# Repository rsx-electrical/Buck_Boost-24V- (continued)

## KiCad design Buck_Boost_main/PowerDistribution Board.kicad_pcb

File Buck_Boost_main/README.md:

# PowerDistributionBoard
 Distribution power to 150A PDP, 20A 12V regulator, 30A 19V regulator + 24V regulator + charger.

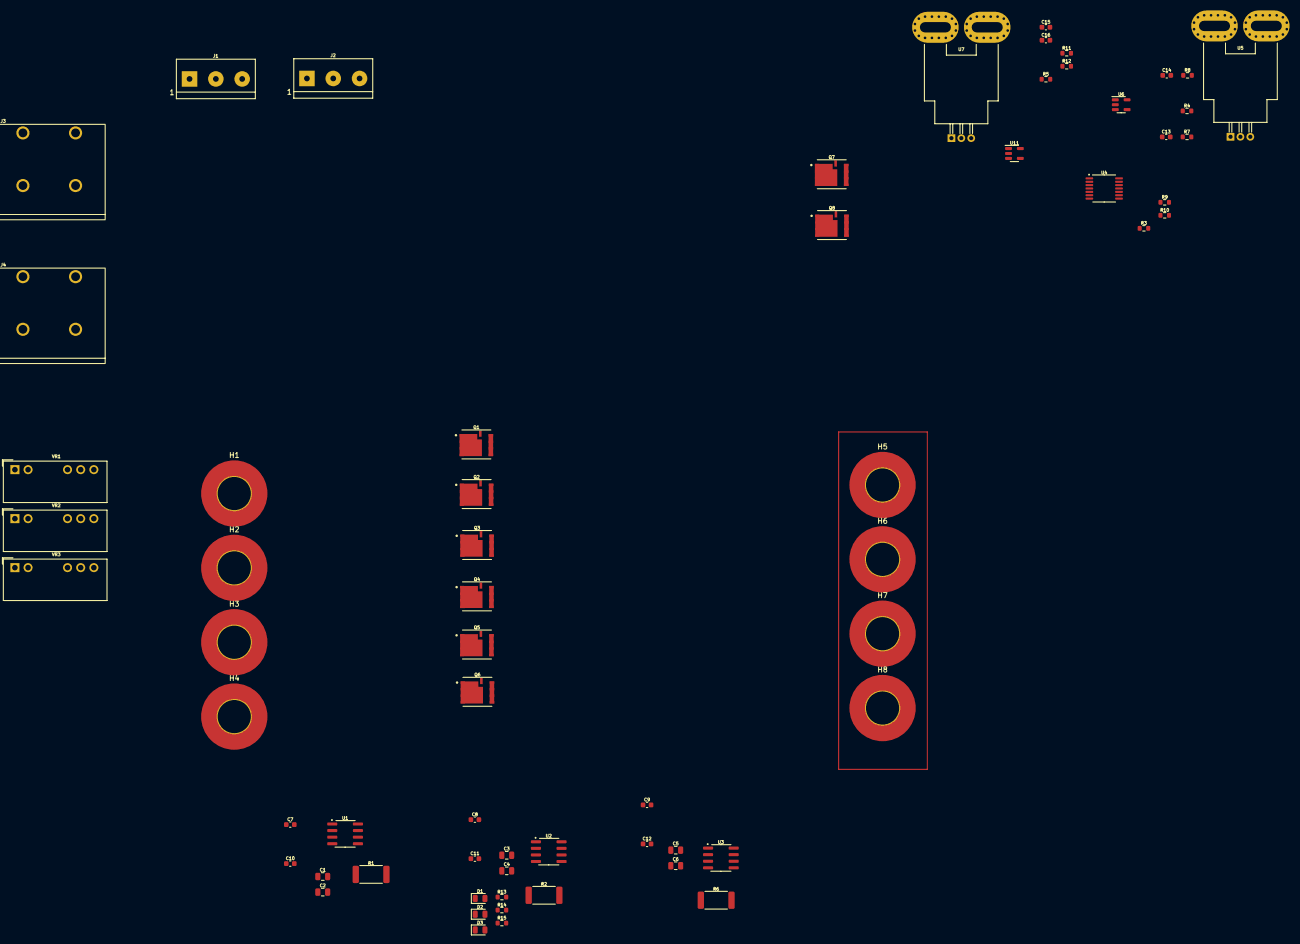
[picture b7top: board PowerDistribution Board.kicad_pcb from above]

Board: 2 copper layers, 65 parts (0 on the bottom side), 41 nets, no tracks yet.

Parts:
C1, C2, C3, C4, C5, C6: 1u; C_0805_2012Metric
C7, C8, C9, C10, C11, C12, C13, C14, C15, C16: 0u1; C_0603_1608Metric
D1, D2, D3: LED_B; LED_0805_2012Metric
H1, H2, H3, H4, H5, H6, H7, H8: MountingHole_Pad; MountingHole_6.4mm_M6_Pad_TopBottom
J1, J2: Screw_Terminal_3x5.08; Molex_0398800303
J3, J4: Screw_Terminal_2x10.16; Amphenol_VP0265540000G
Q1, Q2, Q3, Q4, Q5, Q6, Q7, Q8: IQDH29NE2LM5CG; IFX-PG-TTFN-9-2-V
R1, R2, R6: 1R00_1W; R_2512_6332Metric
R3, R4, R9, R10, R13, R14, R15: 1K; R_0603_1608Metric
R5, R7, R8, R12: 10K; R_0603_1608Metric
R11: 5.6K; R_0603_1608Metric
U1, U2, U3: NCV57080ADR2G; SOIC-8_3.9x4.9mm_P1.27mm_DL
U4: 74HC08; TSSOP-14_4.4x5mm_P0.65mm_DL
U5: ACS758ECB-200U-PFF-T; Allegro_CB_PFF
U6, U11: LMV321A; SOT-23-5
U7: ACS758LCB-050U-PFF-T; Allegro_CB_PFF
VR1, VR2, VR3: NMK1212SAC; Converter_DCDC_muRata_NMKDxxxxSAC_THT

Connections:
12V reg: C4.2, C11.2, J3.1, Q7.1 (S), Q7.2 (S), Q7.3 (S), Q7.4 (S), U2.8 (GND2), VR2.7 (0V)
12V_Gate: Q7.9 (G), R2.2, U2.7 (CLAMP)
12V_Iso_12V: C4.1, C11.1, D2.1 (K), U2.5 (VDD2)
12V_Iso_12V_LED: R14.1, VR2.5 (+Vo)
12V_Iso_19V: C1.1, C10.1, D3.1 (K), U1.5 (VDD2)
12V_Iso_19V_LED: R15.1, VR3.5 (+Vo)
12V_Iso_PDP: C6.1, C12.1, D1.1 (K), U3.5 (VDD2)
12V_Iso_PDP_LED: R13.1, VR1.5 (+Vo)
19V reg: C1.2, C10.2, J3.2, Q8.1 (S), Q8.2 (S), Q8.3 (S), Q8.4 (S), U1.8 (GND2), U7.5 (IP-), VR3.7 (0V)
19V_Gate: Q8.9 (G), R1.2, U1.7 (CLAMP)
30A Ref+: R5.2, R11.1, U11.3 (+)
150A Ref+: R4.2, R7.1, U6.3 (+)
+3V3: C2.1, C3.1, C5.1, C7.1, C8.1, C9.1, C14.2, C16.2, J1.2, R4.1, R5.1, U1.1 (VDD1), U2.1 (VDD1), U3.1 (VDD1), U4.2, U4.5, U4.14 (VCC), U5.1 (VCC), U6.5 (V+), U7.1 (VCC), U11.5 (V+)
+12V: J1.3, VR1.1 (Vin), VR2.1 (Vin), VR3.1 (Vin)
Charger_in: J4.2, U7.4 (IP+)
Enable1: J2.1, U4.13
Enable2: J2.2, R9.1
Enable3: J2.3, U4.10
GND: C2.2, C3.2, C5.2, C7.2, C8.2, C9.2, C13.2, C14.1, C15.2, C16.1, J1.1, R7.2, R11.2, U1.3 (C), U1.4 (GND1), U2.3 (C), U2.4 (GND1), U3.3 (C), U3.4 (GND1), U4.7 (GND), U5.2 (GND), U6.2 (V-), U7.2 (GND), U11.2 (V-), VR1.2 (GND), VR2.2 (GND), VR3.2 (GND)
IN+1: R3.2, U1.2 (A)
IN+2: R9.2, U2.2 (A)
IN+3: R10.2, U3.2 (A)
unnamed: D1.2 (A), R13.2
unnamed: D2.2 (A), R14.2
unnamed: D3.2 (A), R15.2
unnamed: R3.1, U4.11
unnamed: R10.1, U4.8
unnamed: R1.1, U1.6 (VO)
unnamed: R2.1, U2.6 (VO)
unnamed: R6.1, U3.6 (VO)
unnamed: U4.1, U6.1
unnamed: C13.1, R8.1, U5.3 (VOUT)
unnamed: R8.2, U6.4 (-)
unnamed: C15.1, R12.1, U7.3 (VOUT)
unnamed: R12.2, U11.4 (-)
unnamed: U4.4, U11.1
Overcurrent_30A: U4.6, U4.12
Overcurrent_150A: U4.3, U4.9
PDP+: C6.2, C12.2, H5.1, H6.1, H7.1, H8.1, Q1.1 (S), Q1.2 (S), Q1.3 (S), Q1.4 (S), Q2.1 (S), Q2.2 (S), Q2.3 (S), Q2.4 (S), Q3.1 (S), Q3.2 (S), Q3.3 (S), Q3.4 (S), Q4.1 (S), Q4.2 (S), Q4.3 (S), Q4.4 (S), Q5.1 (S), Q5.2 (S), Q5.3 (S), Q5.4 (S), Q6.1 (S), Q6.2 (S), Q6.3 (S), Q6.4 (S), U3.8 (GND2), VR1.7 (0V)
PDP_Gate: Q1.9 (G), Q2.9 (G), Q3.9 (G), Q4.9 (G), Q5.9 (G), Q6.9 (G), R6.2, U3.7 (CLAMP)
Vb+: H1.1, H2.1, H3.1, H4.1, Q1.5 (D), Q1.6 (D), Q1.7 (D), Q1.8 (D), Q2.5 (D), Q2.6 (D), Q2.7 (D), Q2.8 (D), Q3.5 (D), Q3.6 (D), Q3.7 (D), Q3.8 (D), Q4.5 (D), Q4.6 (D), Q4.7 (D), Q4.8 (D), Q5.5 (D), Q5.6 (D), Q5.7 (D), Q5.8 (D), Q6.5 (D), Q6.6 (D), Q6.7 (D), Q6.8 (D), Q7.5 (D), Q7.6 (D), Q7.7 (D), Q7.8 (D), Q8.5 (D), Q8.6 (D), Q8.7 (D), Q8.8 (D), U5.5 (IP-)

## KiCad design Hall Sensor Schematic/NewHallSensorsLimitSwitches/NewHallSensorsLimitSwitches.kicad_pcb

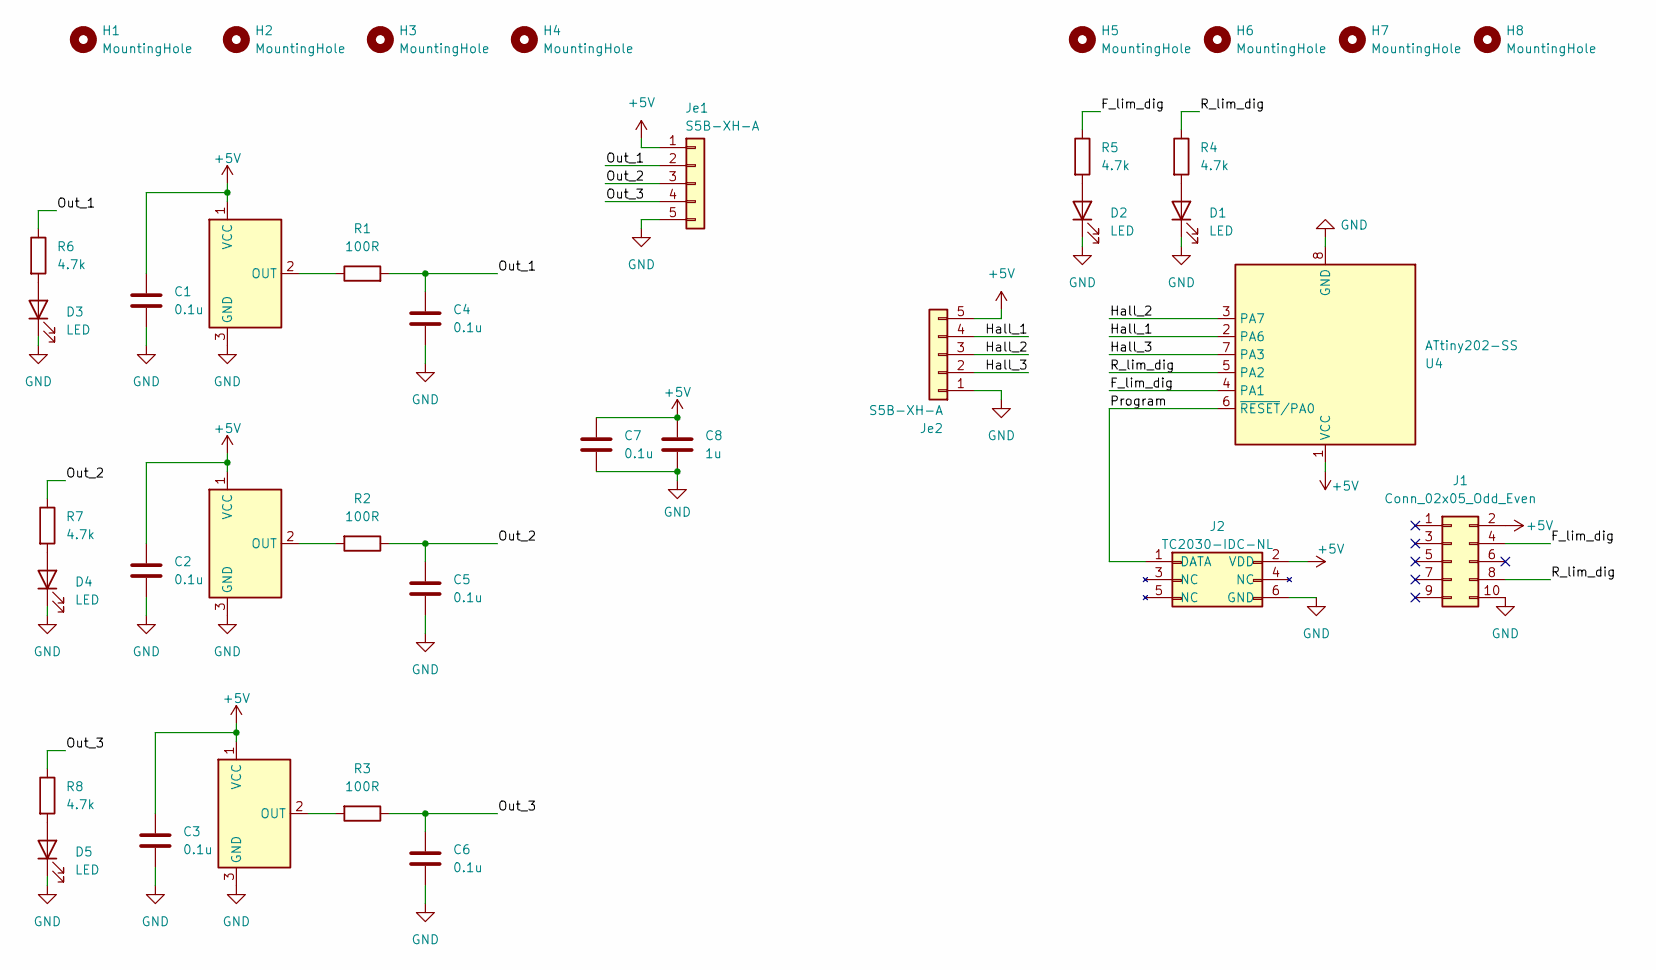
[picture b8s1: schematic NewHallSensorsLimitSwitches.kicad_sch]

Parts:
C1, C2, C3, C4, C5, C6: 0.1u; C_0603_1608Metric
C7: 0.1u; C_0805_2012Metric; MPN CL21B105KAFNFNE
C8: 1u; C_0805_2012Metric; MPN 08055C104KAT2A
D1, D2, D3, D4, D5: LED; LED_0805_2012Metric
H1, H2, H3: MountingHole; MountingHole_2.1mm
H4, H5, H6, H7, H8: MountingHole; MountingHole_2.2mm_M2_DIN965_Pad
J1: Conn_02x05_Odd_Even; Half_Pitch_IDC_2x5
J2: TC2030-IDC-NL; Tag-Connect_TC2030-IDC-NL_2x03_P1.27mm_Vertical
Je1, Je2: S5B-XH-A; JST_PH_S5B-PH-K_1x05_P2.00mm_Horizontal
R1, R2, R3: 100R; R_0603_1608Metric
R4, R5, R6, R7, R8: 4.7k; R_0603_1608Metric
U1, U2, U3: DRV5055A3xDBZxQ1; SOT-23
U4: ATtiny202-SS; SOIC-8_3.9x4.9mm_P1.27mm

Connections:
+5V: C1.1, C2.1, C3.1, C7.1, C8.1, J1.2, J2.2 (VDD), Je1.1, Je2.5, U1.1 (VCC), U2.1 (VCC), U3.1 (VCC), U4.1 (VCC)
/F_lim_dig: J1.4, R5.1, U4.4 (PA1)
/Hall_1: Je2.4, U4.2 (PA6)
/Hall_2: Je2.3, U4.3 (PA7)
/Hall_3: Je2.2, U4.7 (PA3)
/Out_1: C4.1, Je1.2, R1.2, R6.1
/Out_2: C5.1, Je1.3, R2.1, R7.1
/Out_3: C6.1, Je1.4, R3.1, R8.1
/Program: J2.1 (DATA), U4.6 (~RESET/PA0)
/R_lim_dig: J1.8, R4.1, U4.5 (PA2)
GND: C1.2, C2.2, C3.2, C4.2, C5.2, C6.2, C7.2, C8.2, D1.1 (K), D2.1 (K), D3.1 (K), D4.1 (K), D5.1 (K), J1.10, J2.6 (GND), Je1.5, Je2.1, U1.3 (GND), U2.3 (GND), U3.3 (GND), U4.8 (GND)
unnamed: D1.2 (A), R4.2
unnamed: D2.2 (A), R5.2
unnamed: D3.2 (A), R6.2
unnamed: D4.2 (A), R7.2
unnamed: D5.2 (A), R8.2
unnamed: R1.1, U1.2 (OUT)
unnamed: R2.2, U2.2 (OUT)
unnamed: R3.2, U3.2 (OUT)

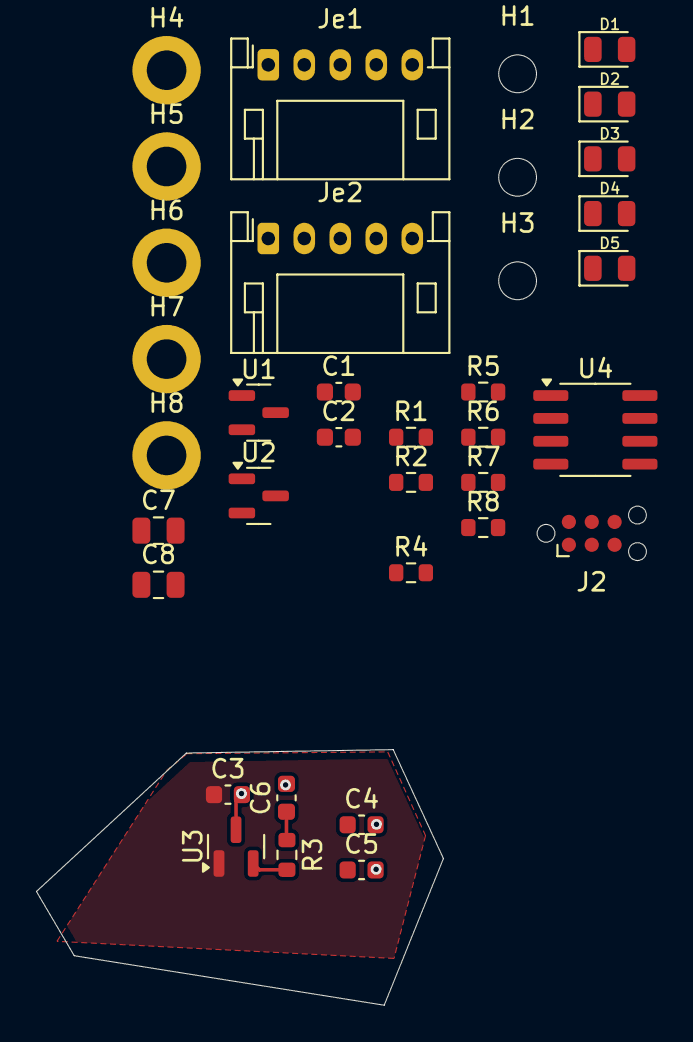
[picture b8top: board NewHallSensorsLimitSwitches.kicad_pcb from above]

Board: 2 copper layers, 22.6 x 14.2 mm, 36 parts (0 on the bottom side), 19 nets.

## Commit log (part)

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2025-11-03 wagabaga bobo
2025-11-03 wawa
2025-11-03 NEW COMMENT RAHHHHHH
2025-11-04 Add files via upload
    Testing if Kicad files show with Github Changes
2025-11-04 Add files via upload
    Checking again if files show up on Kicad
2025-11-06 please let this work
2025-11-06 Finishing another draft of Inverting Buck
2025-11-06 Made a couple of changes, aligned the gnd and vout terminals of the screw terminal and capacitor so at to have a cleaner and wider vout/gnd copper pour, with buck having a larger Iout>Iin, so less po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
    Also went ahead and drew all the passive components for the IC as closer to the main body of the chip as possible, this will come into greater importance later on when working with more complicated P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
    Via placemnt centralized at the capa
2025-11-08 Create readme.txt
    incase we are doing each other's proj in one place
2025-11-08 initial folder name wrong lul
2025-11-08 Boosr ver1?
2025-11-08 Revert "Boosr ver1?"
    This reverts commit 50cfb5769ac7e5a7e117e2f05ce3dbf4331a3901.
2025-11-08 im tweaking
2025-11-11 hello
2025-11-11 Add files via upload
    hello
2025-11-15 hello 2
2025-11-16 Folder for buck
2025-11-20 Maria Boost Practice Schematic
2025-11-22 Boost PCB Board
2025-11-22 Add missing vias
2025-11-22 Schematic only
2025-11-22 Revert "Merge branch 'main' of github.com:rsx-electrical/Buck_Boost-24V-"
    This reverts commit 1544c4365805954bfe84498f9553f0563d02ccfb, reversing
    changes made to f300fd34cac0b3ee4a6897acb38f98237bb70485.
2025-11-22 update1
2025-11-22 final for now
2025-11-22 testing 123
2025-11-27 final update
2026-01-17 test
2026-01-17 Placed in Inductor, Controller, and Fets, along with obligatory heatsink, screw terms, and fuses.
    I realized that we already have an extra 15uh power inductor from the bucks with very low dcr and high sat current (1.62mohm, 16A), so we can use this one:(PQ2614BHA-150K)
2026-01-18 folder restructure
2026-01-18 edit readme to correct .md format
2026-01-18 edit readme to be .md friendly
2026-01-18 get cmds to be highlighted in readme
2026-01-18 add History folder and 4_switch_Buck_Boost readme
2026-01-18 Updated KiCad schematic with selected caps and resistors; saved snapshot to History
2026-02-06 main pwr path
2026-02-07 Reformat to be human readable
2026-02-28 High side switch
2026-02-28 LT spice simulation results in readme
2026-03-06 Adding filtering capacitance values
2026-03-06 Creating LTSpice folder with high side switch test circuit
2026-03-06 LT8390 pins
2026-03-08 Update buck boost feedback circuit, add trimmer and decoupling caps
2026-03-14 finish up schematic before final check
2026-03-14 final schem
2026-03-17 Updated Schematic with cool stuff trust
2026-04-03 Updated the Component Placement
2026-05-23 pcb - lets pray
2026-06-03 Edited component placement. Added general sketch for the power path. Removed some traces.
2026-06-04 controller and auxiliary circuits
